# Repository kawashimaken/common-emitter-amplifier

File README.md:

# common-emitter-amplifier
Common Emitter Amplifier

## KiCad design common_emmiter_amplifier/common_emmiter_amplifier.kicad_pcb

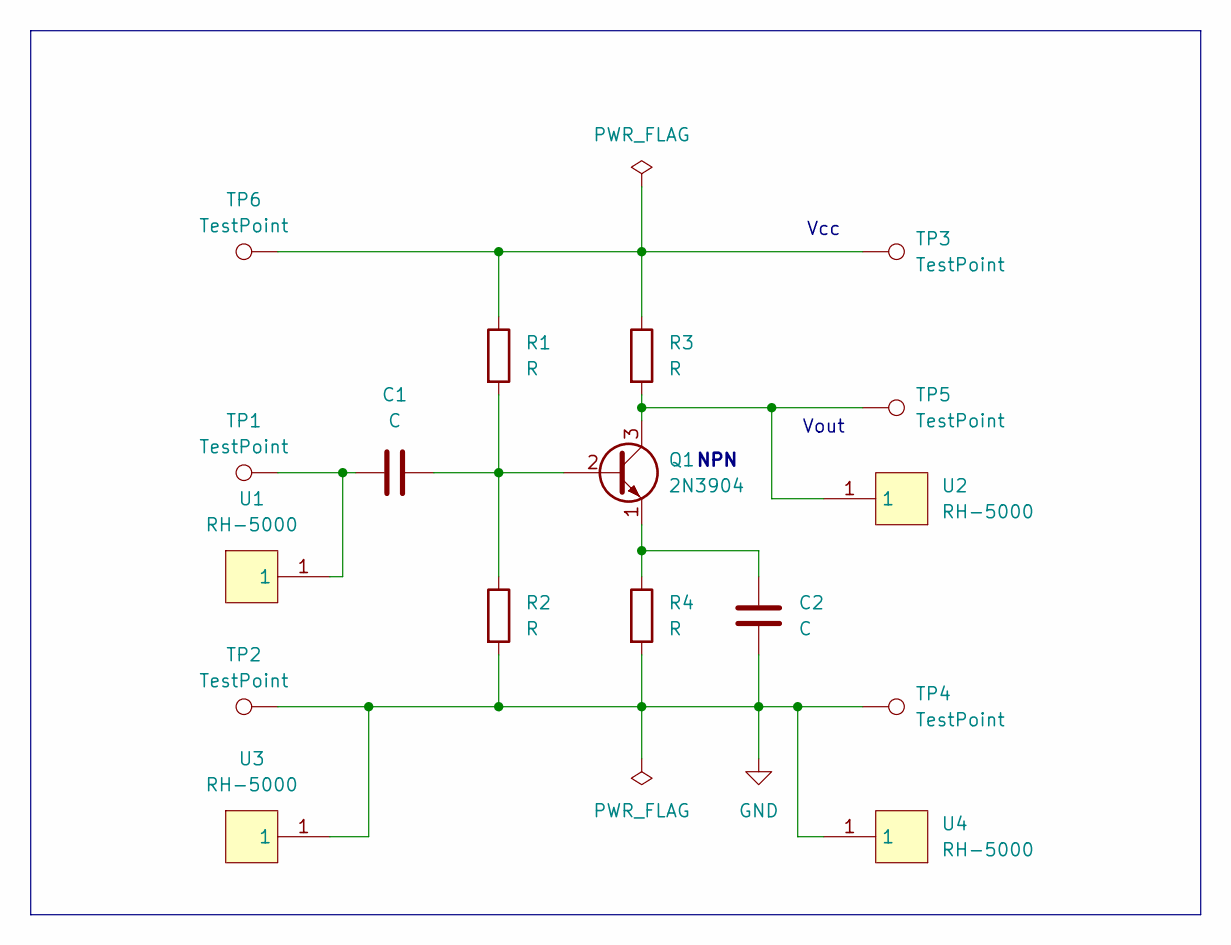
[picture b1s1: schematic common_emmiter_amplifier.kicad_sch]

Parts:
C1, C2: C; C_Disc_D5.0mm_W2.5mm_P2.50mm
Q1: 2N3904; TO-92_Inline
R1, R2, R3, R4: R; R_Axial_DIN0207_L6.3mm_D2.5mm_P7.62mm_Horizontal
TP1, TP2, TP3, TP4, TP5, TP6: TestPoint; TestPoint_THTPad_D3.0mm_Drill1.5mm
U1, U2, U3, U4: RH-5000; TEST-TH_BD2.54-P1.4_RED; LCSC Part C5277086

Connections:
GND: C2.2, R2.2, R4.2, TP2.1, TP4.1, U3.1, U4.1
unnamed: C1.2, TP1.1, U1.1
unnamed: C1.1, Q1.2 (B), R1.2, R2.1
unnamed: Q1.3 (C), R3.2, TP5.1, U2.1
unnamed: C2.1, Q1.1 (E), R4.1
unnamed: R1.1, R3.1, TP3.1, TP6.1

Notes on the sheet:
NPN
Vcc
Vout

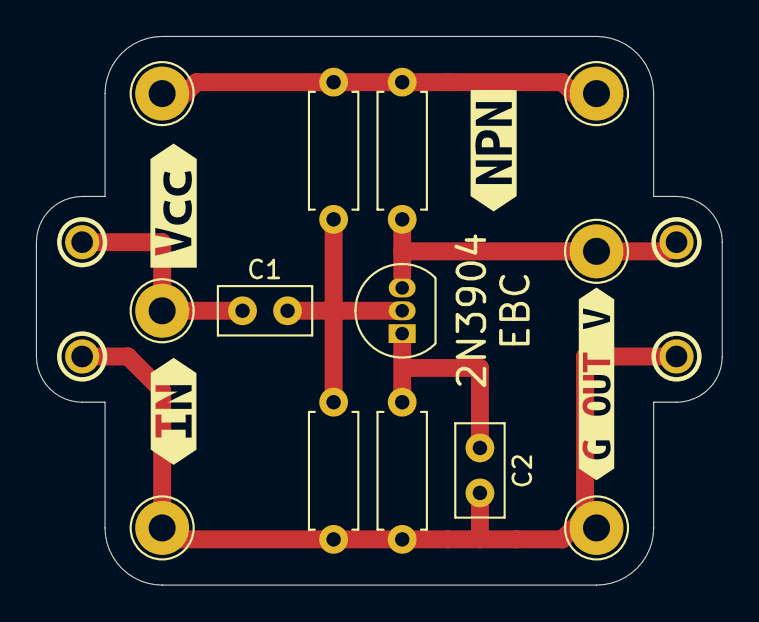
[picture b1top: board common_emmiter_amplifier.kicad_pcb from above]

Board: 2 copper layers, 38.1 x 30.5 mm, 21 parts (0 on the bottom side), 6 nets.

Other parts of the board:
kibuzzard-66C69BD3: G***; kibuzzard-66C69BD3
kibuzzard-66C69C01: G***; kibuzzard-66C69C01
kibuzzard-66C691BF: G***; kibuzzard-66C691BF
kibuzzard-66C6985C: G***; kibuzzard-66C6985C

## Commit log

2024-08-22 could be final version?
